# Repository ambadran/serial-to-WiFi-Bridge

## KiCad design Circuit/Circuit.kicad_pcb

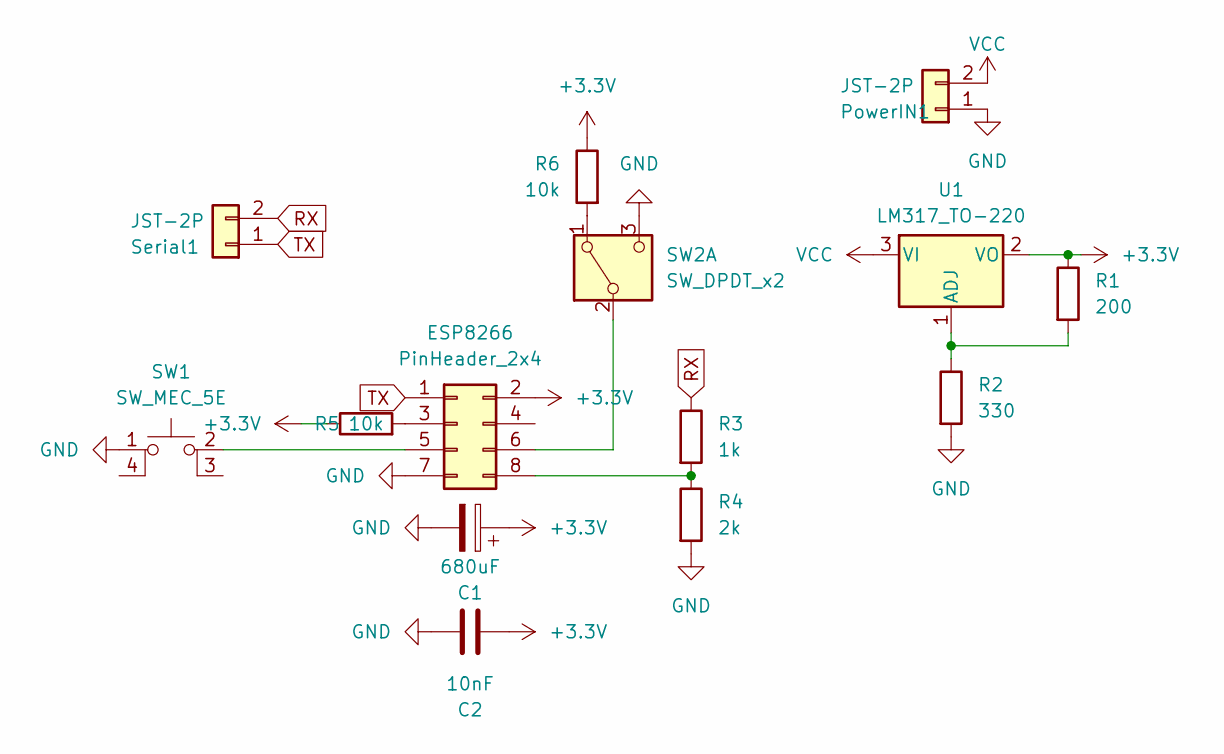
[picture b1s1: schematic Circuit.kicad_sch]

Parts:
C1: 680uF; CP_Radial_D8.0mm_P3.80mm
C2: 10nF; C_Disc_D5.0mm_W2.5mm_P2.50mm
ESP8266: PinHeader_2x4; PinSocket_2x04_P2.54mm_Vertical
PowerIN1: JST-2P; JST_EH_B2B-EH-A_1x02_P2.50mm_Vertical
R1: 200; R_Axial_DIN0207_L6.3mm_D2.5mm_P7.62mm_Horizontal
R2: 330; R_Axial_DIN0207_L6.3mm_D2.5mm_P7.62mm_Horizontal
R3: 1k; R_Axial_DIN0207_L6.3mm_D2.5mm_P7.62mm_Horizontal
R4: 2k; R_Axial_DIN0207_L6.3mm_D2.5mm_P7.62mm_Horizontal
R5, R6: 10k; R_Axial_DIN0207_L6.3mm_D2.5mm_P7.62mm_Horizontal
SW1: SW_MEC_5E; SW_PUSH_6mm
SW2: SW_DPDT_x2; PinSocket_1x03_P2.54mm_Vertical
Serial1: JST-2P; JST_EH_B2B-EH-A_1x02_P2.50mm_Vertical
U1: LM317_TO-220; TO-220-3_Vertical

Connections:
+3.3V: C1.1, C2.1, ESP8266.2, R1.1, R5.1, R6.1, U1.2 (VO)
GND: C1.2, C2.2, ESP8266.7, PowerIN1.1, R2.2, R4.2, SW1.1, SW2.3 (C)
unnamed: ESP8266.3, R5.2
unnamed: ESP8266.5, SW1.2
unnamed: ESP8266.6, SW2.2 (B)
unnamed: ESP8266.8, R3.2, R4.1
unnamed: R6.2, SW2.1 (A)
unnamed: R1.2, R2.1, U1.1 (ADJ)
RX: R3.1, Serial1.2
TX: ESP8266.1, Serial1.1
VCC: PowerIN1.2, U1.3 (VI)

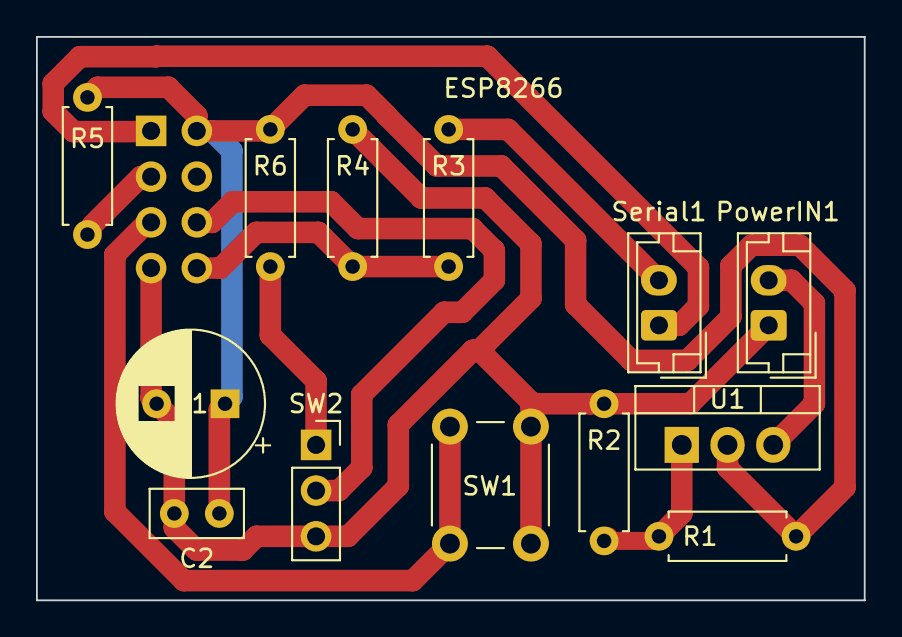
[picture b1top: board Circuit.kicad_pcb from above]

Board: 2 copper layers, 46.0 x 31.3 mm, 14 parts (1 on the bottom side), 11 nets.

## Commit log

2024-08-12 finished initial working script and added schematic
2024-08-15 finsihed PCB layout
